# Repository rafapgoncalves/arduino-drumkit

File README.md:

# arduino-drumkit

An Arduino Nano USB drumkit to play with, but not limited to, [Ubuntu Studio](https://ubuntustudio.org/) 18.04 and [Hydrogen](http://hydrogen-music.org/) 0.9.7.

## Getting Started

1. Download and install Eclipse C/C++. More on that [here](https://www.eclipse.org/community/eclipse_newsletter/2017/april/article4.php);
2. Clone the repository;
3. Open eclipse and create a new workspace;
4. Go to File -> Import -> General -> Existing projects into workspace;
    - Select arduino-drumkit folder and check "Search for nested projects";
    - Make sure all projects are selected and click Finish.

### Arduino

First thing to do is to adjust the code to your arduino's version. Open [arduino/src/drums/Drumkit.cpp](/arduino/src/drums/Drumkit.cpp). 
At the Drumkit constructor you will find the declaration of the sensors (`SwitchSensor` for pull-up switches and `PiezoSensor` for piezos) and keys ([instructions](/KEYS.md)) for each drum pad.

Since I'm using Arduino Nano, the project is set up with 2 switches (one for bass drum and the other for hi-hat pedal) and 8 piezos.

You can change most of the parameters in [arduino/src/Define.h](/arduino/src/Define.h).

#### General MIDI

A few adjustments may be necessary to use it as a GM-compatible instrument:

* Make sure DEBUG messages are disabled;
* Keys may vary as stated [before](/KEYS.md);
* Baud Rate may be different, probably 31250.

### Ubuntu Studio

In order to run ubuntu-studio project you are goint to need read permission on serial port. Run the program as sudo or add your user to dialout group or equivalent. Don't forget to log off and back in for the changes to take effect.

```sh
sudo usermod -a -G dialout username
```

If you want to build ubuntu-studio project yourself, you gonna need some libraries that are not installed by default.

```sh
sudo apt update
sudo apt install libgtk-3-dev libgtkmm-3.0-dev
```

### Hardware

The DIN socket is optional in case you plan to use USB. And if you don't want to use USB, don't forget to add a power supply to Arduino.  

Threre is also a [KiCad](http://kicad-pcb.org/) project that you can use. This is a little bit out of scale and I didn't manage to track down where the problem is (footprint, KiCad, img conversion, etc) so double check before creating your pcb (I resized the final image). Also, your DIN socket will be different than mine.

There are good tutorials on YouTube to make drum pads such as [this](https://www.youtube.com/watch?v=-4BPpfFGcIE) one from Spikenzie.

### Jack Control

Connect your arduino to the PC, open and start ubuntu-studio project.

Open QjackCtl and Hydrogen.
On QjackCtl click the Connections button and go to ALSA tab. Connect arduino output port to hydrogen input port.

On Hydrogen, make sure input mode is set to Drumkit: Tools -> Input Mode -> Drumkit.

## License

This project is licensed under the GNU GENERAL PUBLIC LICENSE - see the [LICENSE](https://github.com/rafapgoncalves/arduino-drumkit/blob/master/LICENSE) file for details.

## Acknowledgments

* [evankale](https://github.com/evankale/ArduinoMidiDrums)
* [Dominique Vandenneucker](http://www.music-software-development.com/midi-tutorial.html)
* [amandaghassaei](https://www.instructables.com/id/Send-and-Receive-MIDI-with-Arduino/)
* [Thiago Teixeira & Jari Suominen](http://www.varal.org/ttymidi/)

## TODO

* Add MIDI Channel support
* Move debug messages to MIDI format

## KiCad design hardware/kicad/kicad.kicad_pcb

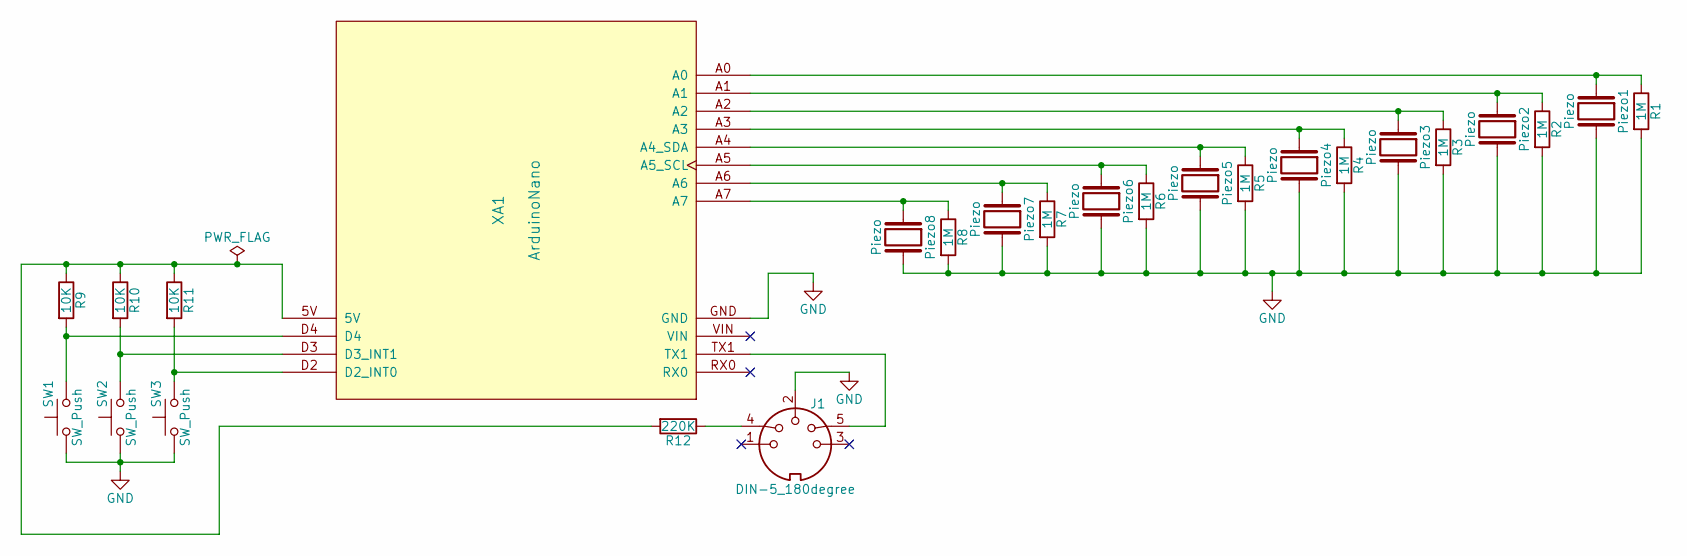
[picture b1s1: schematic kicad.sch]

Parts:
J1: DIN-5_180degree; Din5-180
Piezo1, Piezo2, Piezo3, Piezo4, Piezo5, Piezo6, Piezo7, Piezo8: Piezo; External_2_14.224mm
R1, R2, R3, R4, R5, R6, R7, R8: 1M; R_L6.22mm_D2.3mm_P10.16mm_Horizontal
R9, R10, R11: 10K; R_L6.22mm_D2.3mm_P10.16mm_Horizontal
R12: 220K; R_L6.22mm_D2.3mm_P10.16mm_Horizontal
SW1, SW2, SW3: SW_Push; External_2_14.224mm
XA1: ArduinoNano; ArduinoNanoJacks

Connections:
GND: J1.2, Piezo1.2, Piezo2.2, Piezo3.2, Piezo4.2, Piezo5.2, Piezo6.2, Piezo7.2, Piezo8.2, R1.2, R2.2, R3.2, R4.2, R5.2, R6.2, R7.2, R8.2, SW1.1, SW2.1, SW3.1, XA1.GND
unnamed: J1.4, R12.1
unnamed: J1.5, XA1.TX1
unnamed: Piezo1.1, R1.1, XA1.A0
unnamed: Piezo2.1, R2.1, XA1.A1
unnamed: Piezo3.1, R3.1, XA1.A2
unnamed: Piezo4.1, R4.1, XA1.A3
unnamed: Piezo5.1, R5.1, XA1.A4 (A4_SDA)
unnamed: Piezo6.1, R6.1, XA1.A5 (A5_SCL)
unnamed: Piezo7.1, R7.1, XA1.A6
unnamed: Piezo8.1, R8.1, XA1.A7
unnamed: R9.2, SW1.2, XA1.D4
unnamed: R9.1, R10.1, R11.1, R12.2, XA1.5V
unnamed: R10.2, SW2.2, XA1.D3 (D3_INT1)
unnamed: R11.2, SW3.2, XA1.D2 (D2_INT0)

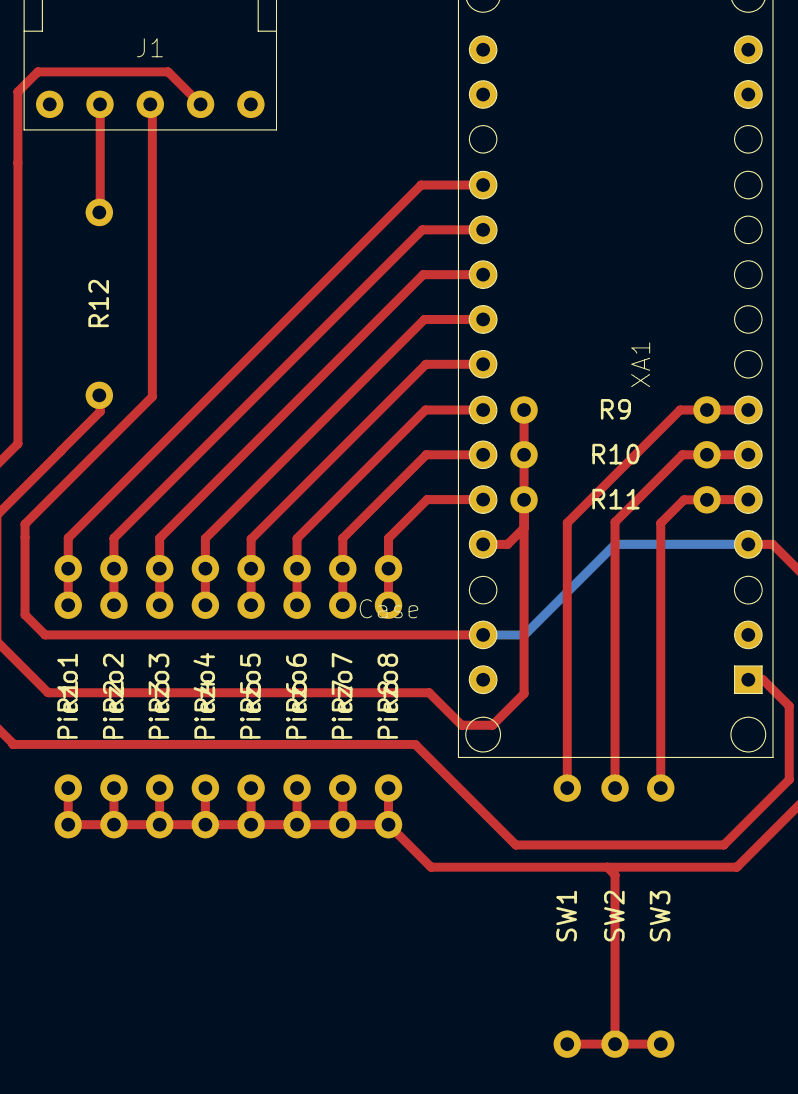
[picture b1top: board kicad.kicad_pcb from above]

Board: 2 copper layers, 26 parts (0 on the bottom side), 15 nets.

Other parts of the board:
Case: Case

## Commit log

2019-11-11 Release 0.0.1.
